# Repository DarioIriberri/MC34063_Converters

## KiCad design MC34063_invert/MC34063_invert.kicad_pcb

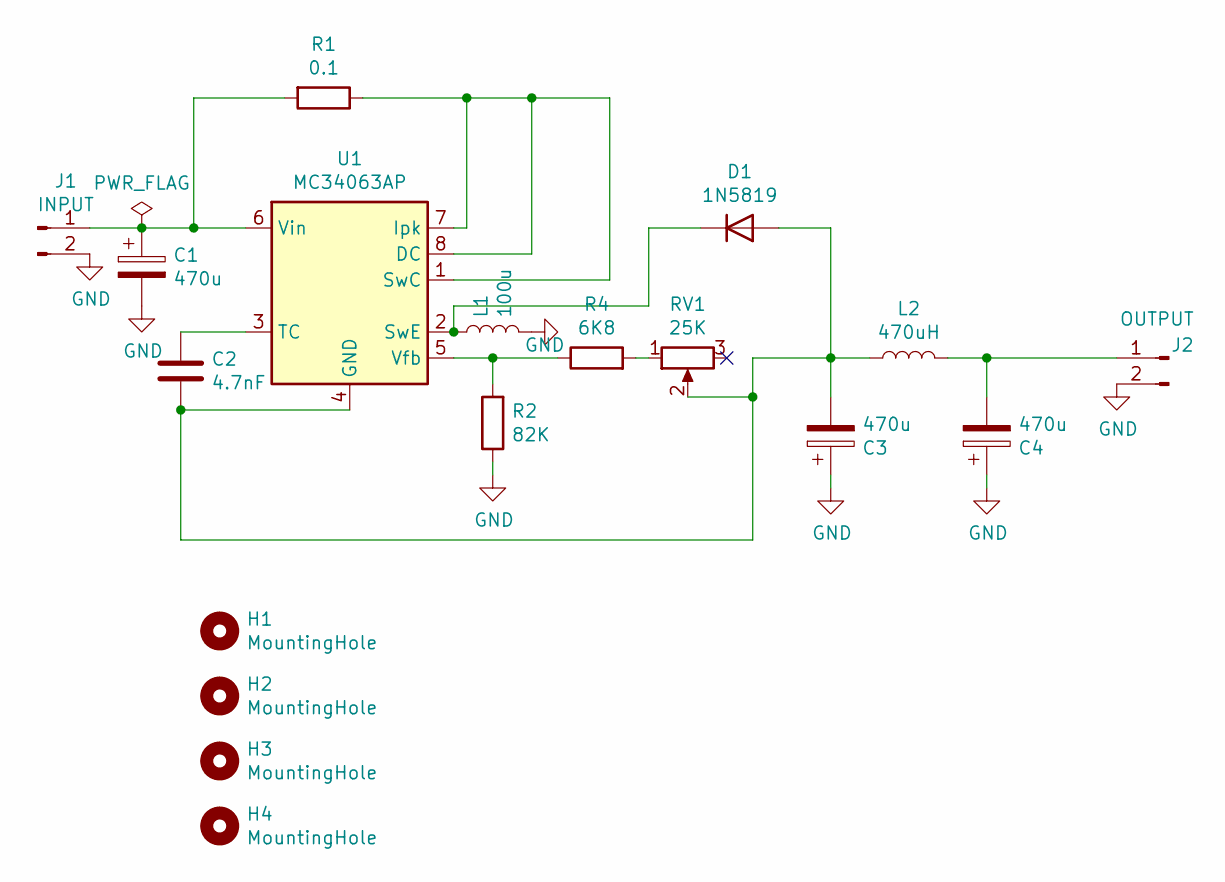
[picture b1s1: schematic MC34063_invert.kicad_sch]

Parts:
C1: 470u; CP_Radial_D8.0mm_P3.50mm
C2: 4.7nF; C_Disc_D7.0mm_W2.5mm_P5.00mm
C3, C4: 470u; CP_Radial_D10.0mm_P5.00mm
D1: 1N5819; D_A-405_P7.62mm_Horizontal
H1, H2, H3, H4: MountingHole; MountingHole_2.2mm_M2
J1: INPUT; TerminalBlock_MetzConnect_Type094_RT03502HBLU_1x02_P5.00mm_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
J2: OUTPUT; TerminalBlock_MetzConnect_Type094_RT03502HBLU_1x02_P5.00mm_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
L1: 100u; L_Toroid_Vertical_L13.0mm_W6.5mm_P5.60mm
L2: 470uH; L_Toroid_Vertical_L13.0mm_W6.5mm_P5.60mm
R1: 0.1; R_Axial_DIN0207_L6.3mm_D2.5mm_P10.16mm_Horizontal
R2: 82K; R_Axial_DIN0207_L6.3mm_D2.5mm_P7.62mm_Horizontal
R4: 6K8; R_Axial_DIN0207_L6.3mm_D2.5mm_P7.62mm_Horizontal
RV1: 25K; Potentiometer_Bourns_3296W_Vertical
U1: MC34063AP; DIP-8_W7.62mm

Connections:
GND: C1.2, C3.1, C4.1, J1.2, J2.2, L1.2, R2.1
unnamed: C2.2, C3.2, D1.2 (A), L2.1, RV1.2, U1.4 (GND)
unnamed: D1.1 (K), L1.1, U1.2 (SwE)
unnamed: C1.1, J1.1, R1.2, U1.6 (Vin)
unnamed: C4.2, J2.1, L2.2
unnamed: R4.2, RV1.1
unnamed: R1.1, U1.1 (SwC), U1.7 (Ipk), U1.8 (DC)
unnamed: C2.1, U1.3 (TC)
unnamed: R2.2, R4.1, U1.5 (Vfb)

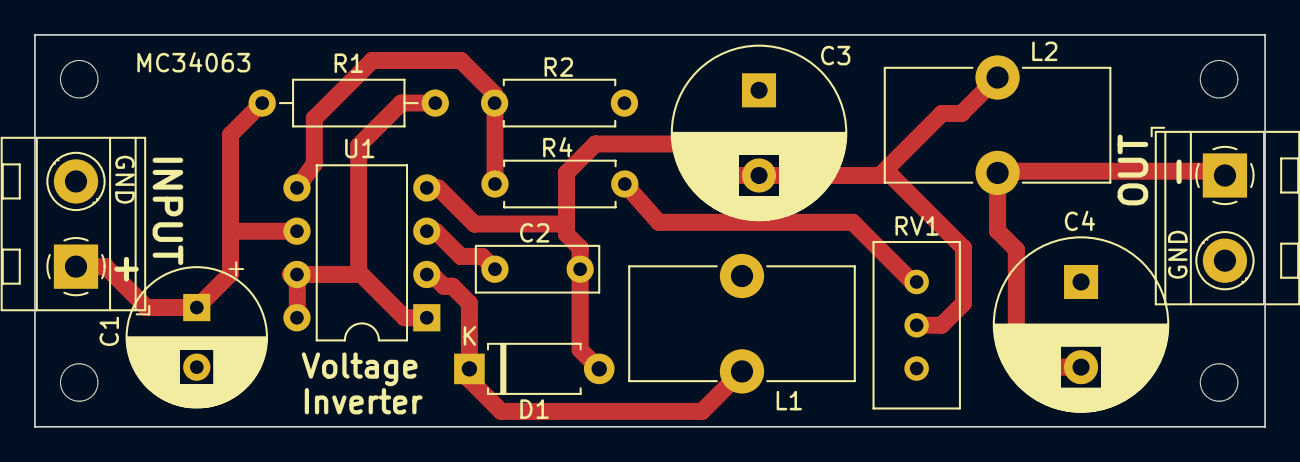
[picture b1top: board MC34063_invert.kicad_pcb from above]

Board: 2 copper layers, 72.2 x 23.0 mm, 18 parts (0 on the bottom side), 9 nets.

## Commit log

2022-12-12 Tweaks
2022-12-12 Gerbers
2022-12-12 Fixed error in feedback loop
2022-12-13 Made buck & inverter PCB's smaller for panelization
2022-12-13 Panelization
2025-03-03 Simplified Inverter
